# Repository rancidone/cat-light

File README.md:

# CatLight

A cat-shaped circuit board with RGB eyes and white LED whiskers. It started as an ESP32 night light, then became **CatLightPocket**, a small battery-powered light I can pin on and wear.

[Photos, video, and the build story](https://mattmadeitwork.com/projects/catlight/)

## CatLightPocket

Pocket uses a CH32V003 with C firmware built on ch32v003fun. It has 24 lighting patterns, including heartbeat, candle, rainbow, and lightning. Tap the button to change patterns; hold it to step through five brightness levels.

- [Firmware, build, and flashing instructions](pocket/README.md)
- [Board designs](pcb/CatLightPocket/)

## Original CatLight

The original is an ESP32 night light, about five inches tall. It serves a browser interface for brightness, lighting modes, and editing Lua patterns. Scripts can run in RAM while experimenting, then be saved to the light.

The ESP32 firmware is retired and has known bugs. Its code and design notes are here for anyone interested in the original build.

- [ESP32 firmware and setup](esp32/README.md)
- Board designs: `pcb/ESPLight-v1.*`

## Build your own

```sh
git clone https://github.com/rancidone/cat-light.git
cd cat-light
```

Follow the guide for your version above. The [hardware guide](docs/building.md) covers assembly, programming connections, and details still needing confirmation before reproducing the boards.

## License

See [LICENSE](LICENSE). ch32v003fun has its own license.

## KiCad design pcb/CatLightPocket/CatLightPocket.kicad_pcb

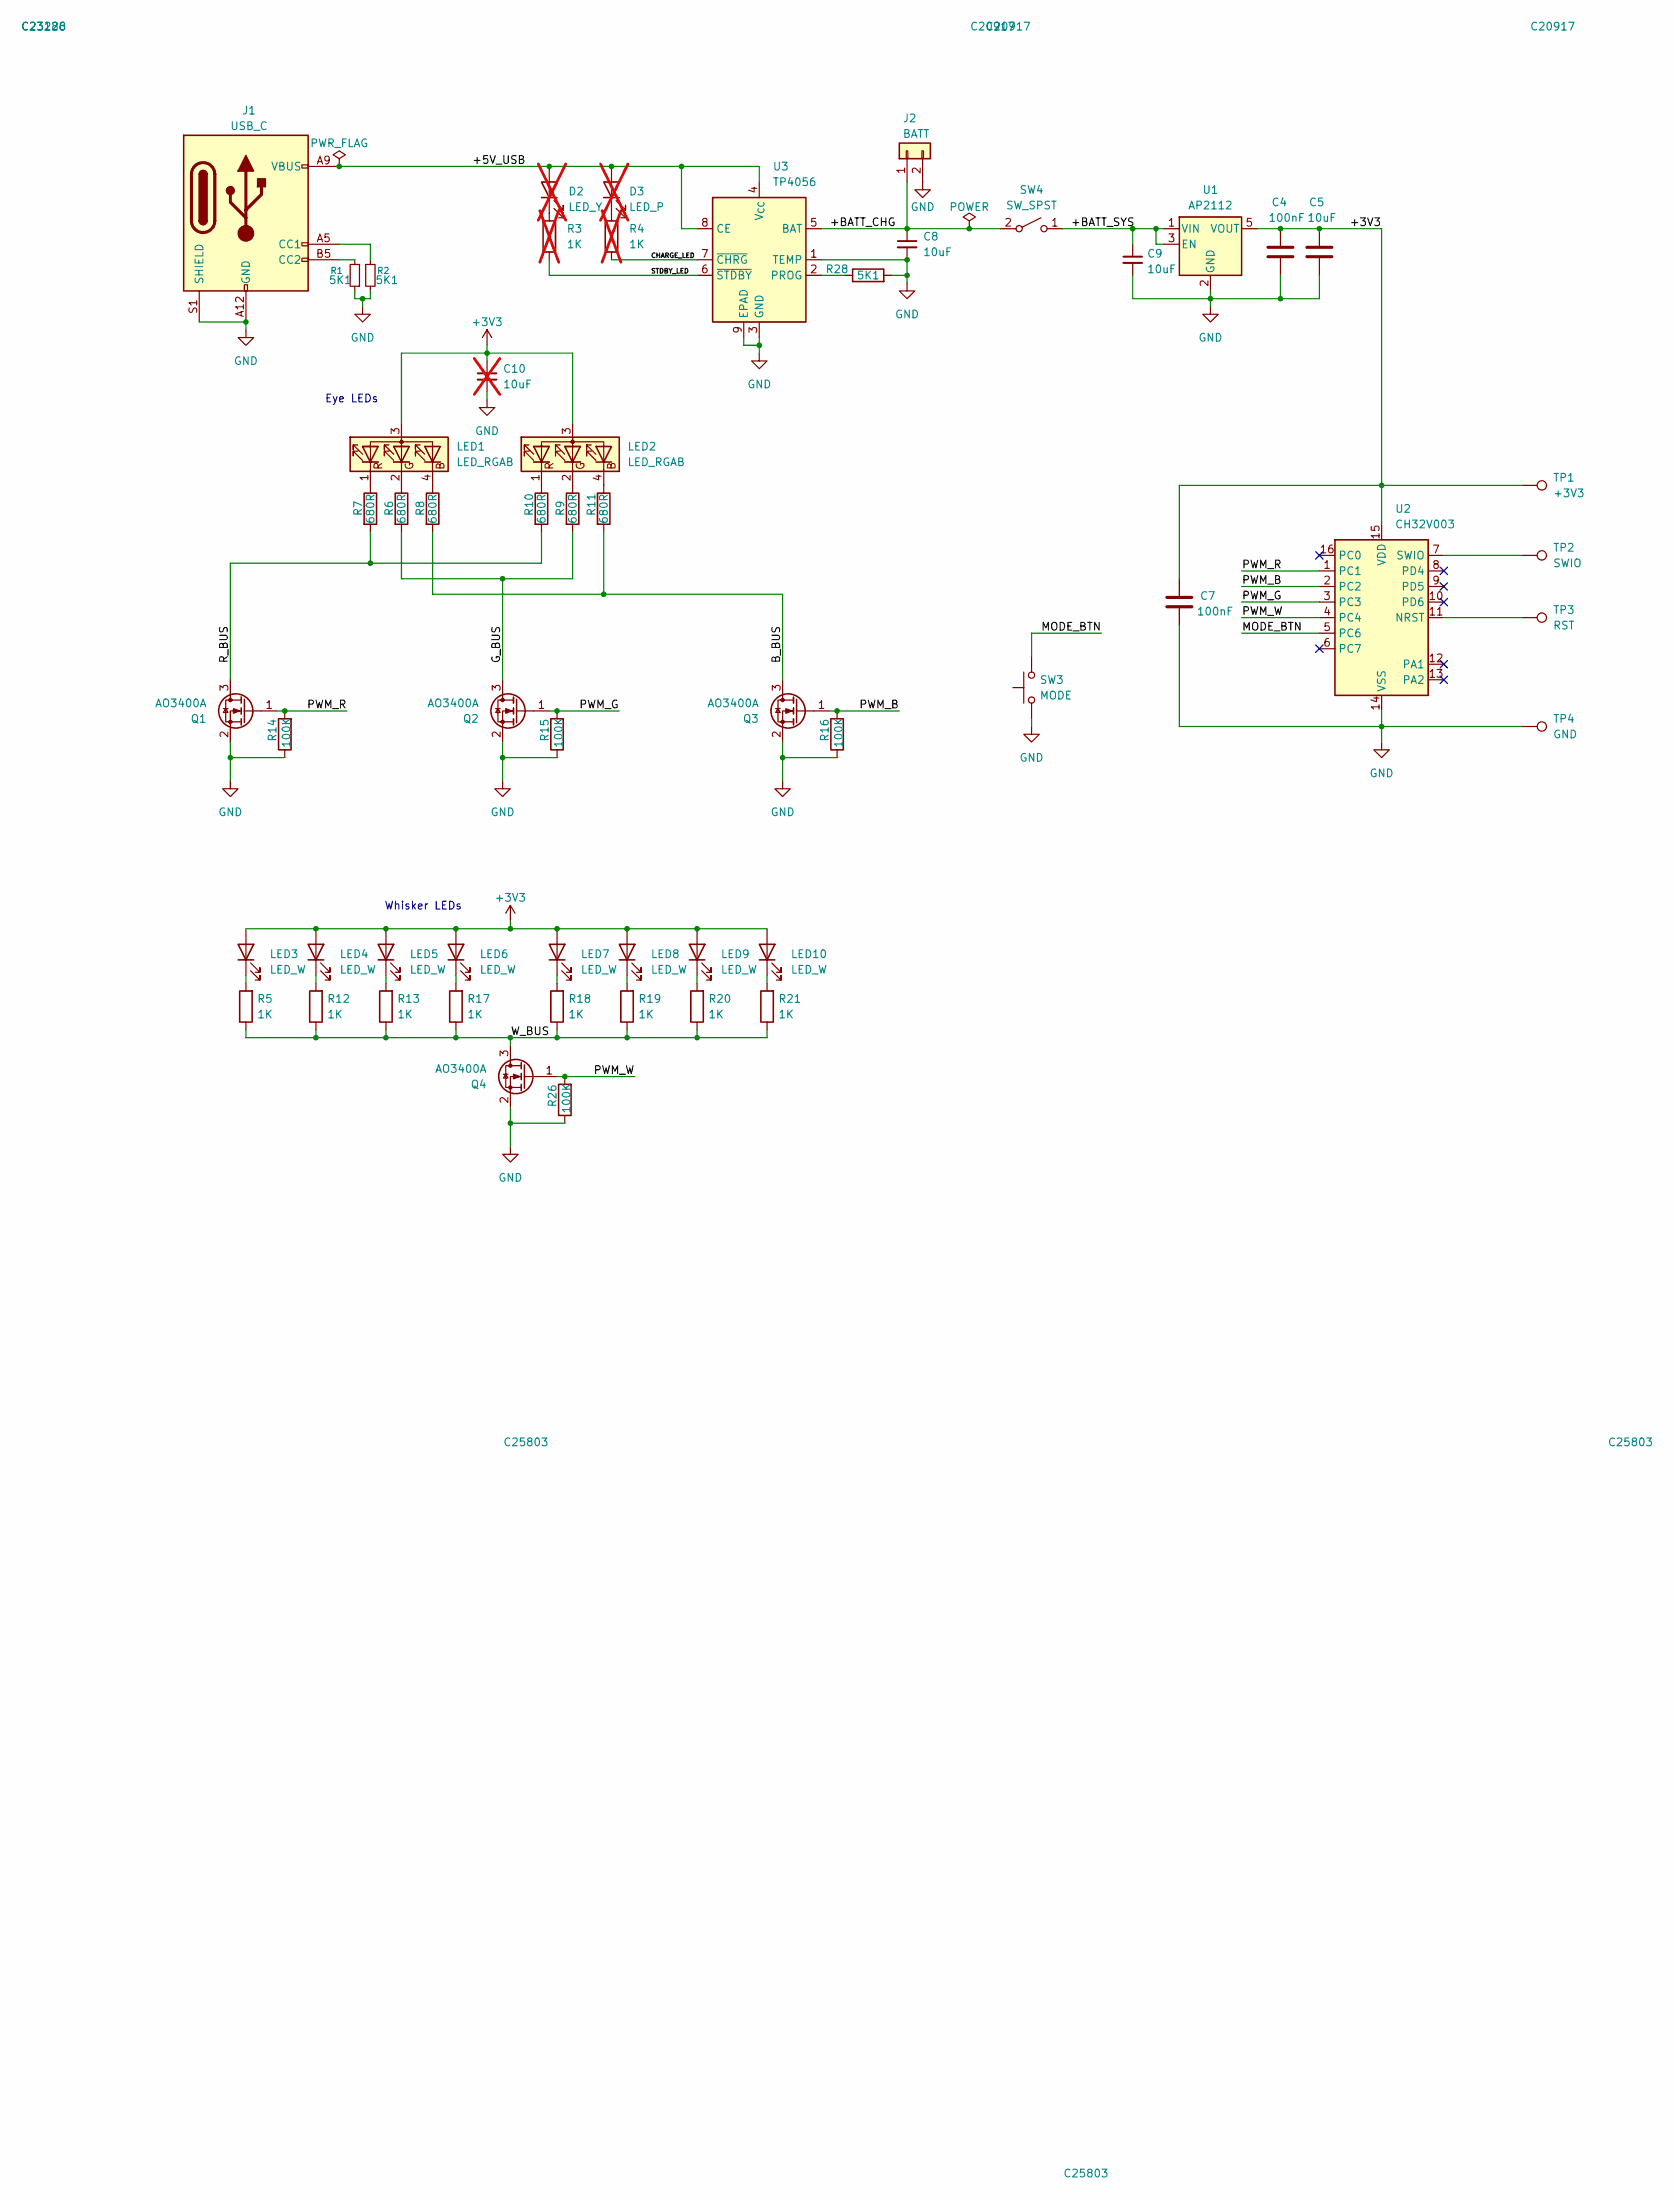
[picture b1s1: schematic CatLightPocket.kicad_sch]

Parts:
C4, C7: 100nF; C_0603_1608Metric_Pad1.08x0.95mm_HandSolder; LCSC C14663
C5: 10uF; C_0805_2012Metric_Pad1.18x1.45mm_HandSolder; LCSC C15850
C8, C9: 10uF; C_0805_2012Metric_Pad1.18x1.45mm_HandSolder
C10: 10uF; C_0805_2012Metric_Pad1.18x1.45mm_HandSolder; not fitted
D2: LED_Y; LED_0603_1608Metric_Pad1.05x0.95mm_HandSolder; not fitted
D3: LED_P; LED_0603_1608Metric_Pad1.05x0.95mm_HandSolder; not fitted
J1: USB_C; USB_C_Receptacle_HRO_TYPE-C-31-M-17
J2: BATT; JST_PH_B2B-PH-K_1x02_P2.00mm_Vertical
LED1, LED2: LED_RGAB; 0805 ARGB LED
LED3, LED4, LED5, LED6, LED7, LED8, LED9, LED10: LED_W; LED_0603_1608Metric_Pad1.05x0.95mm_HandSolder
Q1, Q2, Q3, Q4: AO3400A; SOT-23; LCSC C20917
R1, R2, R28: 5K1; R_0603_1608Metric_Pad0.98x0.95mm_HandSolder; LCSC C23186
R3, R4: 1K; R_0603_1608Metric_Pad0.98x0.95mm_HandSolder; LCSC C21190; not fitted
R5, R12, R13, R17, R18, R19, R20, R21: 1K; R_0603_1608Metric_Pad0.98x0.95mm_HandSolder; LCSC C21190
R6, R7, R8, R9, R10, R11: 680R; R_0603_1608Metric_Pad0.98x0.95mm_HandSolder; LCSC C23228
R14, R15, R16, R26: 100K; R_0603_1608Metric_Pad0.98x0.95mm_HandSolder; LCSC C25803
SW3: MODE; 6x3.5 Tactile Switch
SW4: SW_SPST; SW-MSK12C02
TP1: +3V3; TestPoint_Pad_D2.0mm
TP2: SWIO; TestPoint_Pad_D2.0mm
TP3: RST; TestPoint_Pad_D2.0mm
TP4: GND; TestPoint_Pad_D2.0mm
U1: AP2112; SOT-23-5_HandSoldering
U2: CH32V003; SOIC-16_3.9x9.9mm_P1.27mm
U3: TP4056; SOIC-8-1EP_3.9x4.9mm_P1.27mm_EP2.41x3.3mm; LCSC C16581

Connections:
+3V3: C4.1, C5.1, C7.1, C10.1, LED1.3 (A), LED2.3 (A), LED3.2 (A), LED4.2 (A), LED5.2 (A), LED6.2 (A), LED7.2 (A), LED8.2 (A), LED9.2 (A), LED10.2 (A), TP1.1 (1_1), U1.5 (VOUT), U2.15 (VDD)
/+5V_USB: D2.2 (A), D3.2 (A), J1.A9 (VBUS), J1.B9 (VBUS), U3.4 (V_{CC}), U3.8 (CE)
/+BATT_CHG: C8.1, J2.1, SW4.2 (A), U3.5 (BAT)
/+BATT_SYS: C9.1, SW4.1 (B), U1.1 (VIN), U1.3 (EN)
/B_BUS: Q3.3 (D), R8.2, R11.2
/CHARGE_LED: R4.1, U3.7 (~CHRG)
/G_BUS: Q2.3 (D), R6.2, R9.2
/MODE_BTN: SW3.2, U2.5 (PC6)
/PWM_B: Q3.1 (G), R16.2, U2.2 (PC2)
/PWM_G: Q2.1 (G), R15.2, U2.3 (PC3)
/PWM_R: Q1.1 (G), R14.2, U2.1 (PC1)
/PWM_W: Q4.1 (G), R26.2, U2.4 (PC4)
/R_BUS: Q1.3 (D), R7.2, R10.2
/STDBY_LED: R3.1, U3.6 (~STDBY)
/W_BUS: Q4.3 (D), R5.1, R12.1, R13.1, R17.1, R18.1, R19.1, R20.1, R21.1
GND: C4.2, C5.2, C7.2, C8.2, C9.2, C10.2, J1.A12 (GND), J1.B12 (GND), J1.S1 (SHIELD), J2.2, Q1.2 (S), Q2.2 (S), Q3.2 (S), Q4.2 (S), R1.1, R2.2, R14.1, R15.1, R16.1, R26.1, R28.2, SW3.1, TP4.1 (1_1), U1.2 (GND), U2.14 (VSS), U3.1 (TEMP), U3.3 (GND), U3.9 (EPAD)
unnamed: D2.1 (K), R3.2
unnamed: D3.1 (K), R4.2
unnamed: J1.A5 (CC1), R2.1
unnamed: J1.B5 (CC2), R1.2
unnamed: LED1.4 (BK), R8.1
unnamed: LED1.2 (GK), R6.1
unnamed: LED1.1 (RK), R7.1
unnamed: LED2.4 (BK), R11.1
unnamed: LED2.2 (GK), R9.1
unnamed: LED2.1 (RK), R10.1
unnamed: LED3.1 (K), R5.2
unnamed: LED4.1 (K), R12.2
unnamed: LED5.1 (K), R13.2
unnamed: LED6.1 (K), R17.2
unnamed: LED7.1 (K), R18.2
unnamed: LED8.1 (K), R19.2
unnamed: LED9.1 (K), R20.2
unnamed: LED10.1 (K), R21.2
unnamed: TP2.1 (1_1), U2.7 (SWIO)
unnamed: TP3.1 (1_1), U2.11 (NRST)
unnamed: R28.1, U3.2 (PROG)

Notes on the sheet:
Eye LEDs
Whisker LEDs

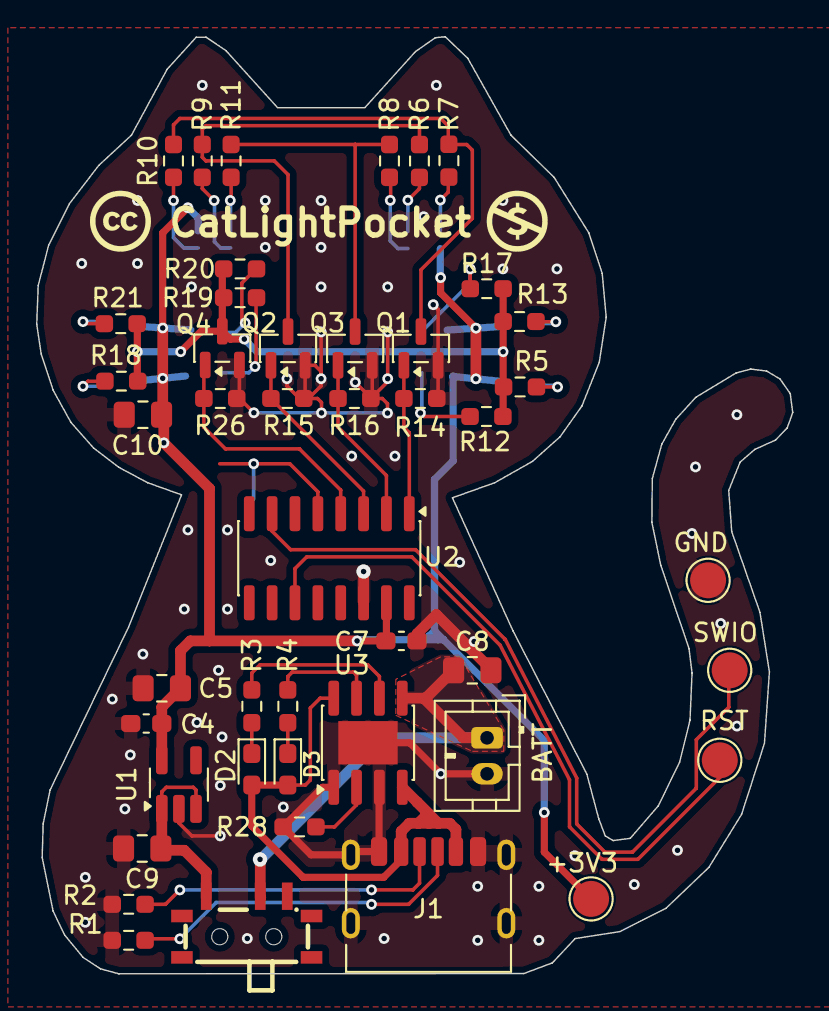
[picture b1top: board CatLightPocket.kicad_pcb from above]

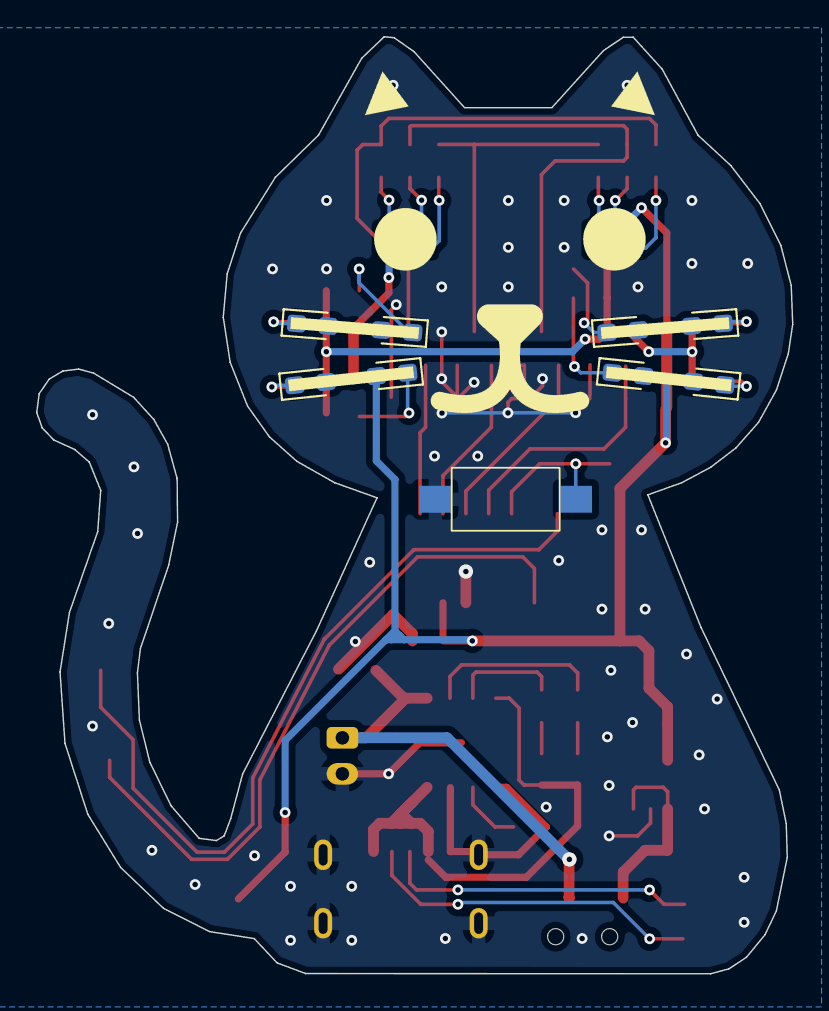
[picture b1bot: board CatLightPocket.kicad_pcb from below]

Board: 2 copper layers, 42.0 x 52.1 mm, 56 parts (11 on the bottom side), 37 nets.

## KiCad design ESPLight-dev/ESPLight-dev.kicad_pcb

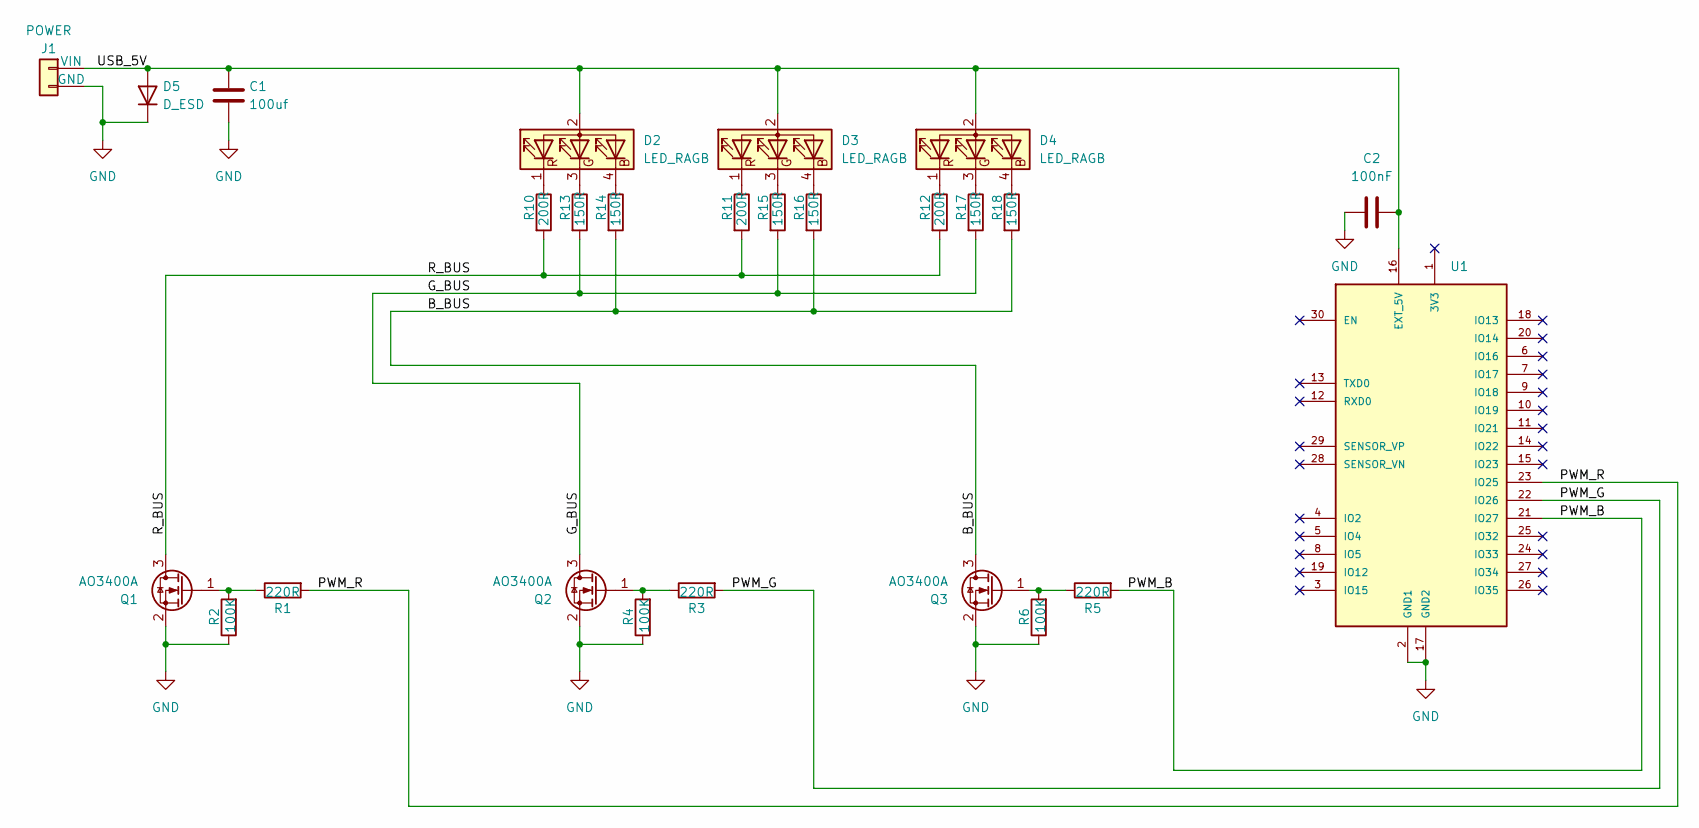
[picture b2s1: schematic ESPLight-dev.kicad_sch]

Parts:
C1: 100uf; C_Radial_D6.3mm_H5.0mm_P2.50mm
C2: 100nF; C_0603_1608Metric
D2, D3, D4: LED_RAGB; LED_D5.0mm-4_RGB
D5: D_ESD; D_SOD-523
J1: POWER; PinHeader_1x02_P2.54mm_Vertical
Q1, Q2, Q3: AO3400A; SOT-23
R1, R3, R5: 220R; R_0603_1608Metric
R2, R4, R6: 100K; R_0603_1608Metric
R10, R11, R12: 200R; R_0603_1608Metric
R13, R14, R15, R16, R17, R18: 150R; R_0603_1608Metric
U1: DEVKIT_V1_ESP32-WROOM-32; ESP32_30pin

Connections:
/B_BUS: Q3.3 (D), R14.2, R16.2, R18.2
/G_BUS: Q2.3 (D), R13.2, R15.2, R17.2
/PWM_B: R5.2, U1.21 (IO27)
/PWM_G: R3.2, U1.22 (IO26)
/PWM_R: R1.2, U1.23 (IO25)
/R_BUS: Q1.3 (D), R10.2, R11.2, R12.2
/USB_5V: C1.1, C2.2, D2.2 (A), D3.2 (A), D4.2 (A), D5.2 (A), J1.1 (VIN), U1.16 (EXT_5V)
GND: C1.2, C2.1, D5.1 (K), J1.2 (GND), Q1.2 (S), Q2.2 (S), Q3.2 (S), R2.1, R4.1, R6.1, U1.2 (GND1), U1.17 (GND2)
unnamed: D2.4 (BK), R14.1
unnamed: D2.3 (GK), R13.1
unnamed: D2.1 (RK), R10.1
unnamed: D3.4 (BK), R16.1
unnamed: D3.3 (GK), R15.1
unnamed: D3.1 (RK), R11.1
unnamed: D4.4 (BK), R18.1
unnamed: D4.3 (GK), R17.1
unnamed: D4.1 (RK), R12.1
unnamed: Q1.1 (G), R1.1, R2.2
unnamed: Q2.1 (G), R3.1, R4.2
unnamed: Q3.1 (G), R5.1, R6.2

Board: 2 copper layers, 26 parts (0 on the bottom side), 20 nets, no tracks yet.

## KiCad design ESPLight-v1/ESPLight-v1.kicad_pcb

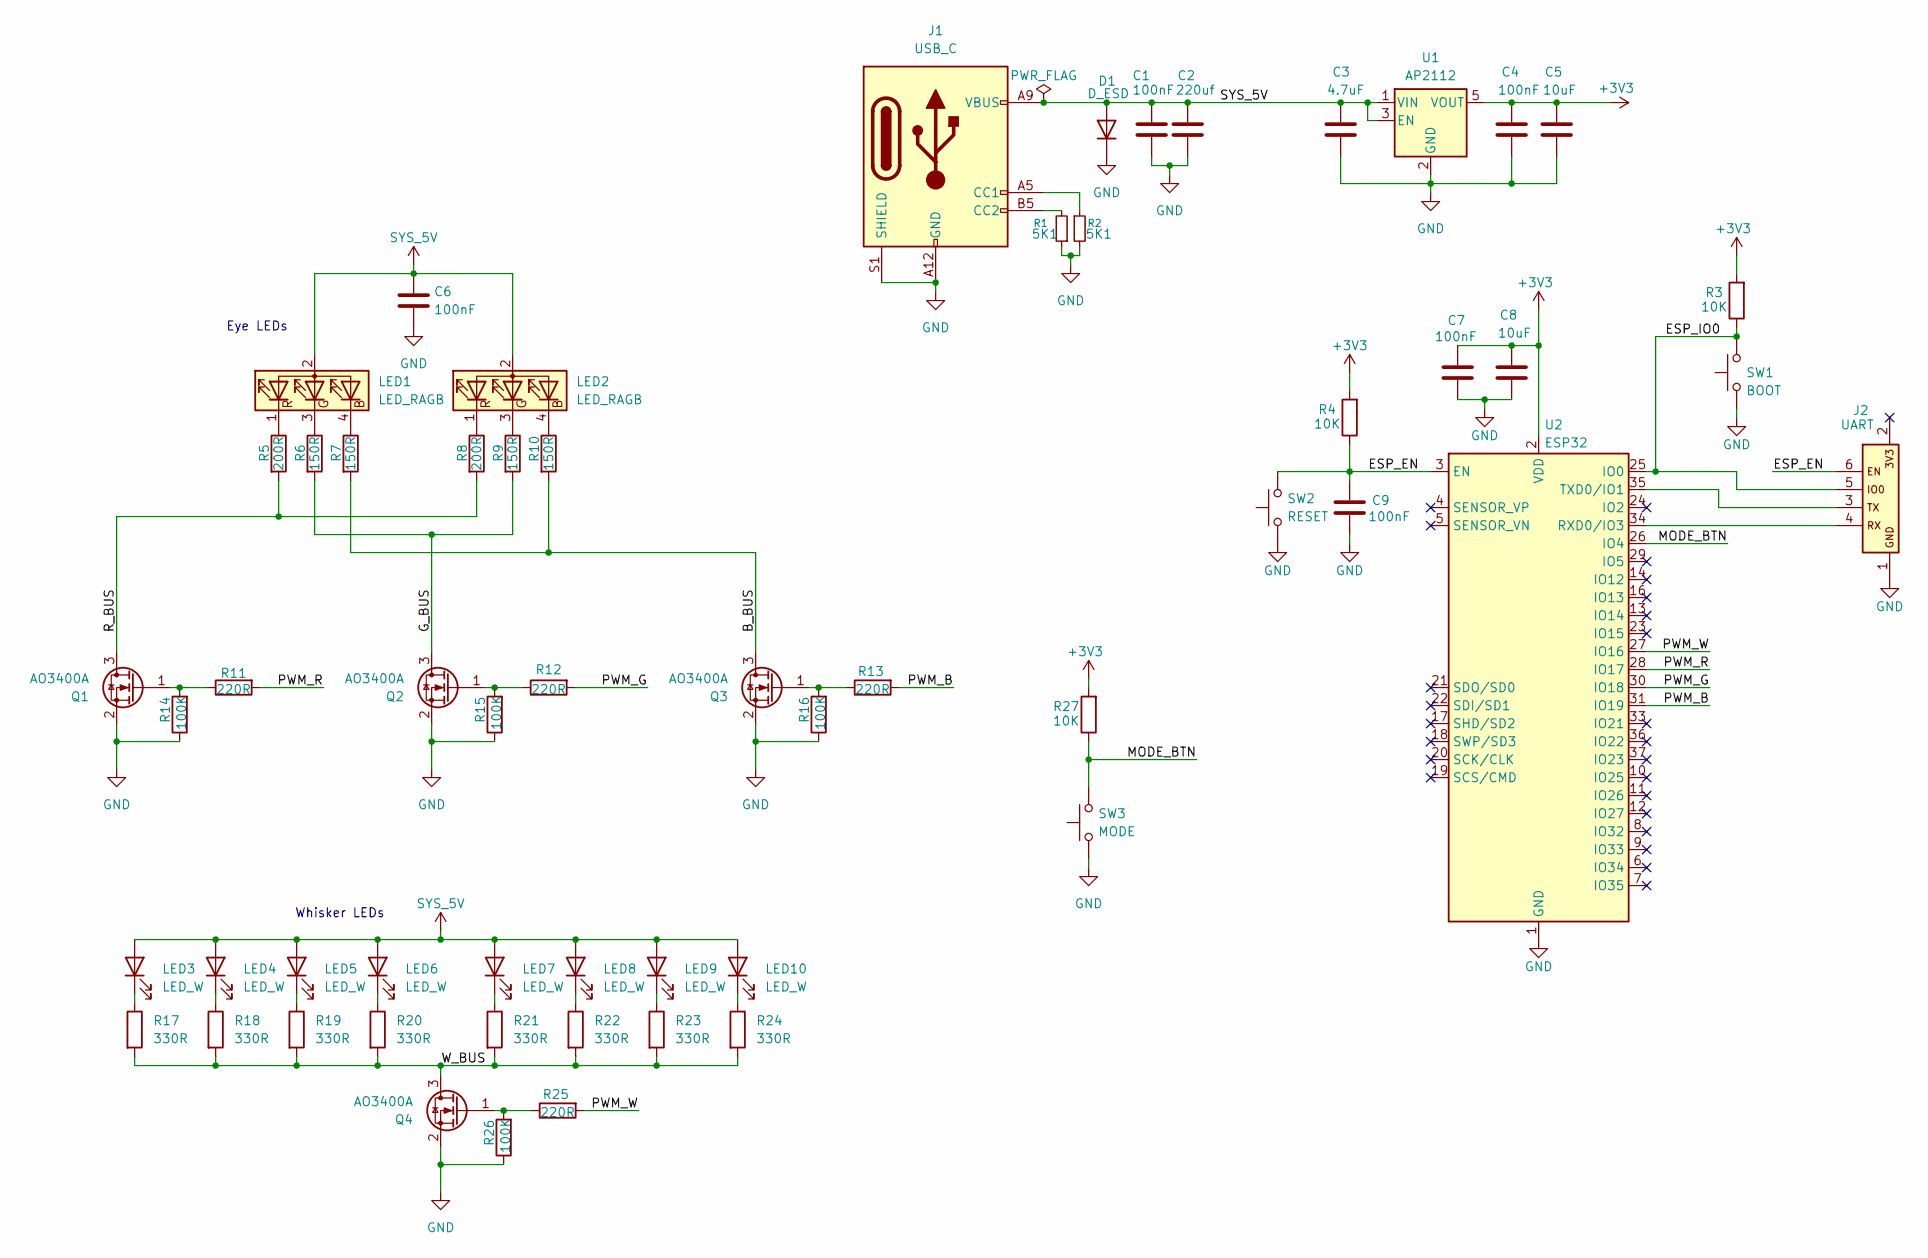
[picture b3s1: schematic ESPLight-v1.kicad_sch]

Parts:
C1, C4, C6, C7, C9: 100nF; C_0603_1608Metric_Pad1.08x0.95mm_HandSolder
C2: 220uf; C_Radial_D6.3mm_H5.0mm_P2.50mm
C3: 4.7uF; C_0805_2012Metric_Pad1.18x1.45mm_HandSolder
C5, C8: 10uF; C_0805_2012Metric_Pad1.18x1.45mm_HandSolder
D1: D_ESD; D_SOD-523
J1: USB_C; USB_C_Receptacle_HRO_TYPE-C-31-M-17
J2: UART; PinHeader_2x03_P2.54mm_Horizontal
LED1, LED2: LED_RAGB; LED_D5.0mm-4_RGB
LED3, LED4, LED5, LED6, LED7, LED8, LED9, LED10: LED_W; LED_0603_1608Metric_Pad1.05x0.95mm_HandSolder
Q1, Q2, Q3, Q4: AO3400A; SOT-23
R1, R2: 5K1; R_0603_1608Metric_Pad0.98x0.95mm_HandSolder
R3, R4, R27: 10K; R_0603_1608Metric_Pad0.98x0.95mm_HandSolder
R5, R8: 200R; R_0603_1608Metric_Pad0.98x0.95mm_HandSolder
R6, R7, R9, R10: 150R; R_0603_1608Metric_Pad0.98x0.95mm_HandSolder
R11, R12, R13, R25: 220R; R_0603_1608Metric_Pad0.98x0.95mm_HandSolder
R14, R15, R16, R26: 100K; R_0603_1608Metric_Pad0.98x0.95mm_HandSolder
R17, R18, R19, R20, R21, R22, R23, R24: 330R; R_0603_1608Metric_Pad0.98x0.95mm_HandSolder
SW1: BOOT; SW_Tactile_SPST_6x3.5mm
SW2: RESET; SW_Tactile_SPST_6x3.5mm
SW3: MODE; SW_Tactile_SPST_6x3.5mm
U1: AP2112; SOT-23-5_HandSoldering
U2: ESP32; ESP32-WROOM-32_NoThermal

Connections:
+3V3: C4.1, C5.1, C7.1, C8.1, R3.2, R4.2, R27.2, U1.5 (VOUT), U2.2 (VDD)
/B_BUS: Q3.3 (D), R7.2, R10.2
/ESP_EN: C9.1, J2.6 (EN), R4.1, SW2.2, U2.3 (EN)
/ESP_IO0: J2.5 (IO0), R3.1, SW1.2, U2.25 (IO0)
/G_BUS: Q2.3 (D), R6.2, R9.2
/MODE_BTN: R27.1, SW3.2, U2.26 (IO4)
/PWM_B: R13.2, U2.31 (IO19)
/PWM_G: R12.2, U2.30 (IO18)
/PWM_R: R11.2, U2.28 (IO17)
/PWM_W: R25.2, U2.27 (IO16)
/R_BUS: Q1.3 (D), R5.2, R8.2
/W_BUS: Q4.3 (D), R17.2, R18.2, R19.2, R20.2, R21.2, R22.2, R23.2, R24.2
GND: C1.2, C2.2, C3.2, C4.2, C5.2, C6.2, C7.2, C8.2, C9.2, D1.1 (K), J1.A12 (GND), J1.B12 (GND), J1.S1 (SHIELD), J2.1 (GND), Q1.2 (S), Q2.2 (S), Q3.2 (S), Q4.2 (S), R1.1, R2.2, R14.1, R15.1, R16.1, R26.1, SW1.1, SW2.1, SW3.1, U1.2 (GND), U2.1 (GND), U2.15 (GND), U2.38 (GND), U2.39 (GND)
unnamed: J1.A5 (CC1), R2.1
unnamed: J1.B5 (CC2), R1.2
unnamed: J2.4 (RX), U2.34 (RXD0/IO3)
unnamed: J2.3 (TX), U2.35 (TXD0/IO1)
unnamed: LED1.4 (BK), R7.1
unnamed: LED1.3 (GK), R6.1
unnamed: LED1.1 (RK), R5.1
unnamed: LED2.4 (BK), R10.1
unnamed: LED2.3 (GK), R9.1
unnamed: LED2.1 (RK), R8.1
unnamed: LED3.1 (K), R17.1
unnamed: LED4.1 (K), R18.1
unnamed: LED5.1 (K), R19.1
unnamed: LED6.1 (K), R20.1
unnamed: LED7.1 (K), R21.1
unnamed: LED8.1 (K), R22.1
unnamed: LED9.1 (K), R23.1
unnamed: LED10.1 (K), R24.1
unnamed: Q1.1 (G), R11.1, R14.2
unnamed: Q2.1 (G), R12.1, R15.2
unnamed: Q3.1 (G), R13.1, R16.2
unnamed: Q4.1 (G), R25.1, R26.2
SYS_5V: C1.1, C2.1, C3.1, C6.1, D1.2 (A), J1.A9 (VBUS), J1.B9 (VBUS), LED1.2 (A), LED2.2 (A), LED3.2 (A), LED4.2 (A), LED5.2 (A), LED6.2 (A), LED7.2 (A), LED8.2 (A), LED9.2 (A), LED10.2 (A), U1.1 (VIN), U1.3 (EN)

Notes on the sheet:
Eye LEDs
Whisker LEDs

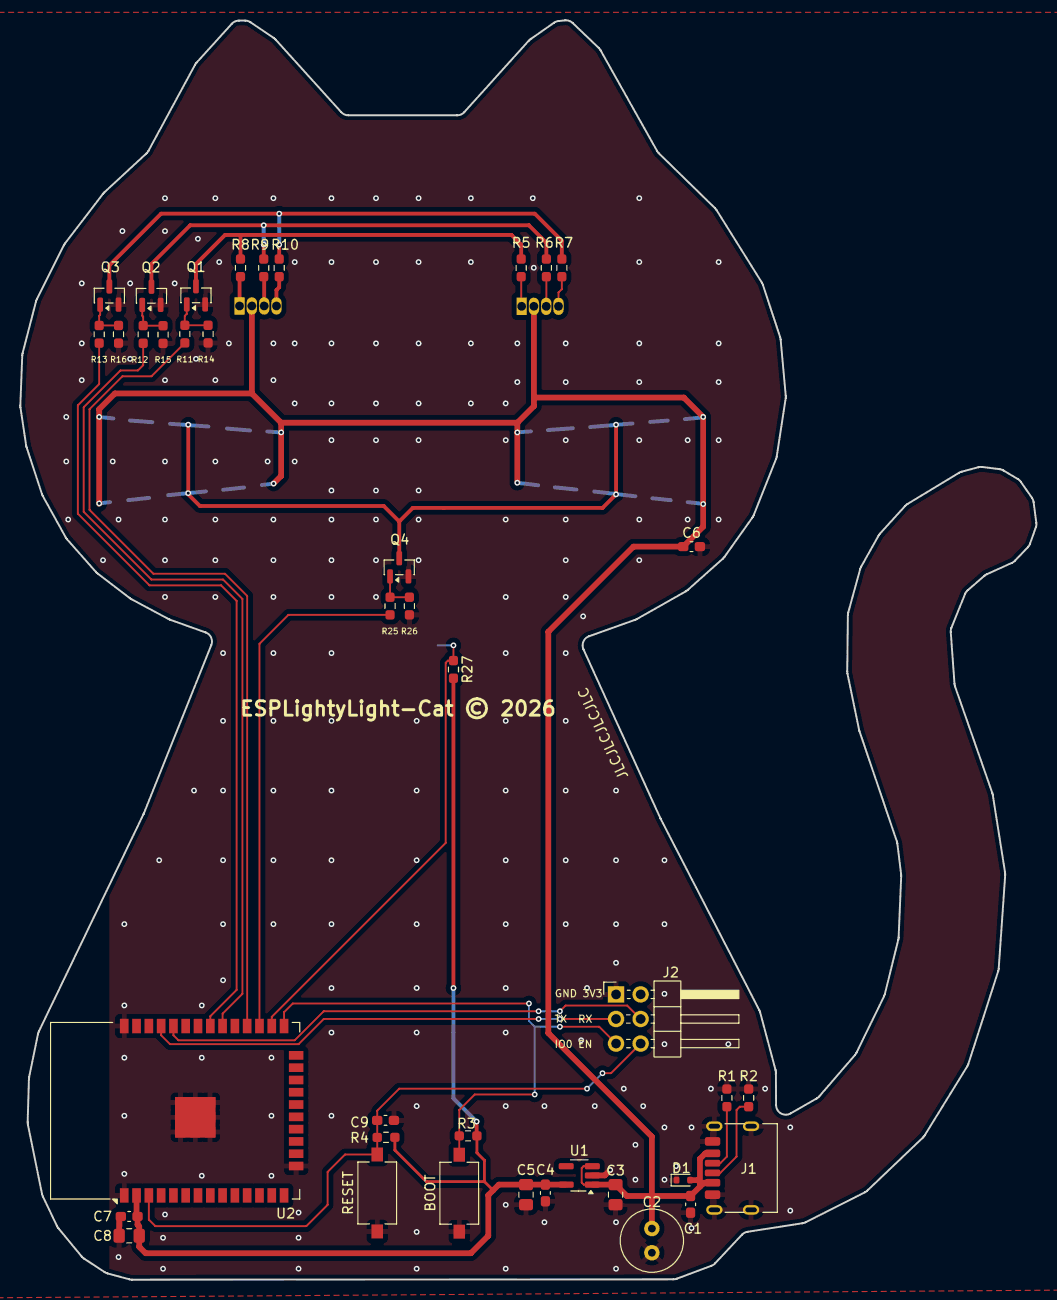
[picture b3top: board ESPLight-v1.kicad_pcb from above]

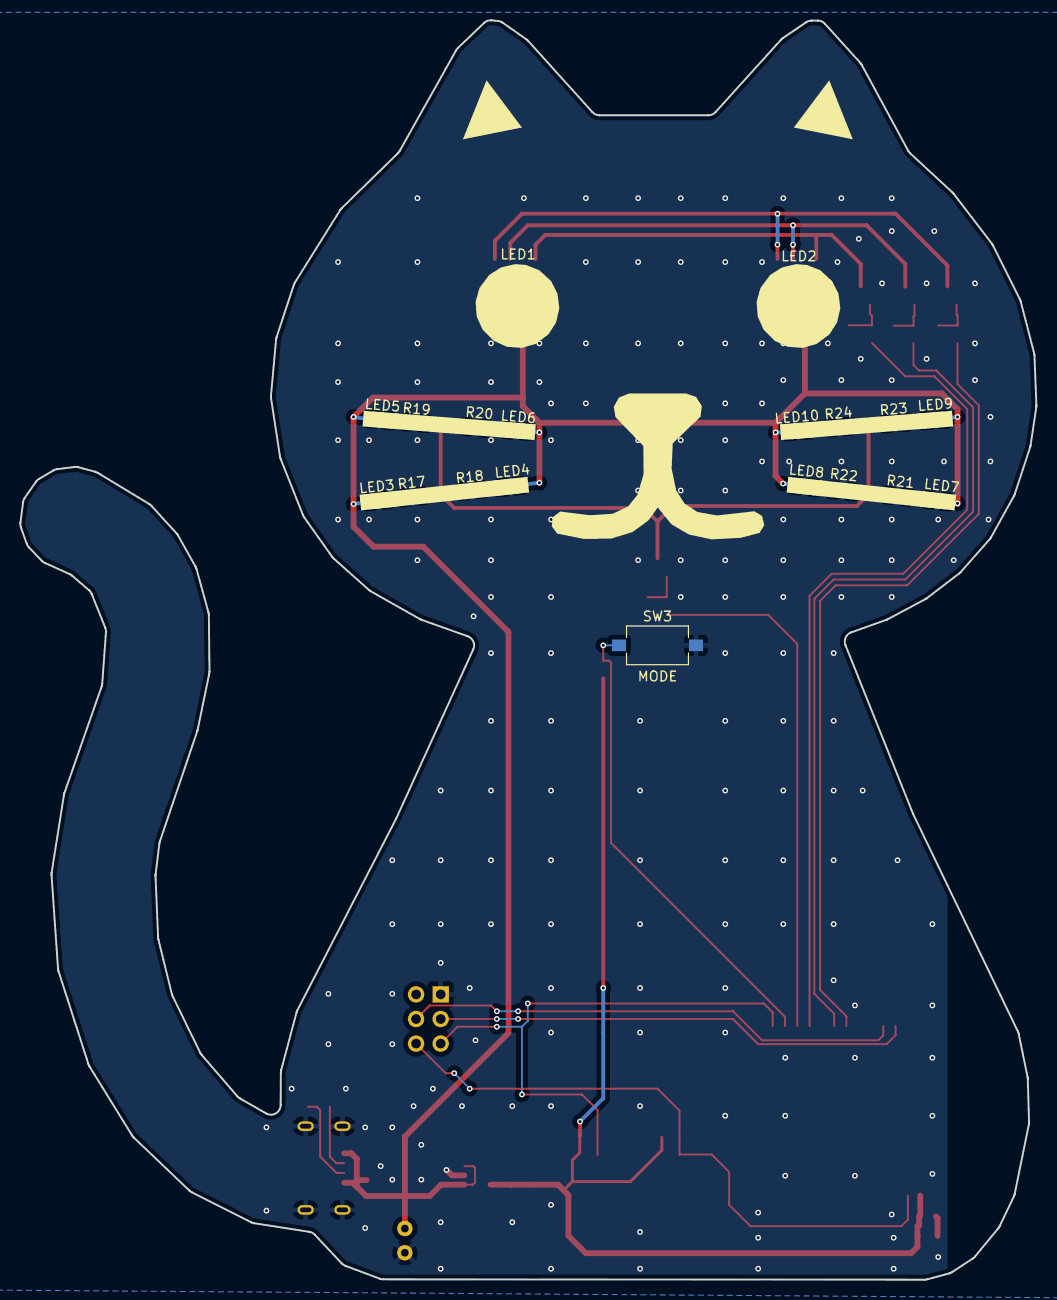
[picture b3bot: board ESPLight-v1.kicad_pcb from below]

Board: 2 copper layers, 105.0 x 130.1 mm, 58 parts (19 on the bottom side), 36 nets.

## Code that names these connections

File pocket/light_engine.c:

#include "light_engine.h"
#include "ch32v003fun/ch32fun/ch32fun.h"

/*
 * Pin assignments (confirmed from schematic):
 *   PC1 → PWM_R  (TIM2 CH4, partial remap 1)
 *   PC2 → PWM_B  (TIM2 CH2, partial remap 1)
 *   PC3 → PWM_G  (TIM1 CH3, no remap)
 *   PC4 → PWM_W  (TIM1 CH4, no remap)
 *   PC6 → MODE_BTN (input, active low, external pull-up)
 *
 * PWM: 48 MHz / (PSC+1) / (ARR+1) = 48e6 / 1 / 4800 = 10 kHz
 */

#define PWM_ARR 4799u

static float s_brightness = 0.30f; /* medium — index 2 of 5 */

static inline uint32_t duty(uint8_t val)  { return (uint32_t)(val  * s_brightness * PWM_ARR / 255u); }
static inline uint32_t dutyf(float v)     { return (uint32_t)(v    * s_brightness * 0.5f * PWM_ARR); }

void light_engine_set_brightness(float b) { s_brightness = b; }

void light_engine_init(void)
{
    /* Clocks */
    RCC->APB2PCENR |= RCC_APB2Periph_GPIOC | RCC_APB2Periph_AFIO | RCC_APB2Periph_TIM1;
    RCC->APB1PCENR |= RCC_APB1Periph_TIM2;

    /* TIM2 partial remap 1: CH2→PC2, CH4→PC1 */
    AFIO->PCFR1 = (AFIO->PCFR1 & ~AFIO_PCFR1_TIM2_REMAP) | AFIO_PCFR1_TIM2_REMAP_PARTIALREMAP1;

    /* GPIO: PC1/PC2/PC3/PC4 → AF push-pull 50 MHz (CNF=10, MODE=11 → 0xB) */
    uint32_t cfg = GPIOC->CFGLR;
    cfg &= ~(0xFFFFu << 4);   /* clear PC1..PC4 nibbles */
    cfg |= (0xBBBBu << 4);    /* set all four to AF push-pull */
    /* PC6 → input with pull-up (CNF=10, MODE=00 → 0x8), OUTDR bit set for pull-up */
    cfg &= ~(0xFu << 24);
    cfg |= (0x8u << 24);
    GPIOC->CFGLR = cfg;
    GPIOC->OUTDR |= (1u << 6); /* enable internal pull-up on PC6 */

    /* TIM2: CH2 (PWM_B / PC2) and CH4 (PWM_R / PC1) */
    TIM2->PSC    = 0;
    TIM2->ATRLR  = PWM_ARR;
    /* CH2 PWM mode 1, preload enable — OC2M at [14:12], OC2PE at [11] */
    TIM2->CHCTLR1 = (0x6u << 12) | (1u << 11);
    /* CH4 PWM mode 1, preload enable — OC4M at [14:12], OC4PE at [11] */
    TIM2->CHCTLR2 = (0x6u << 12) | (1u << 11);
    TIM2->CCER   = TIM_CC2E | TIM_CC4E;
    TIM2->CH2CVR = 0;
    TIM2->CH4CVR = 0;
    TIM2->CTLR1  = TIM_ARPE | TIM_CEN;

    /* TIM1: CH3 (PWM_G / PC3) and CH4 (PWM_W / PC4), no remap */
    TIM1->PSC    = 0;
    TIM1->ATRLR  = PWM_ARR;
    /* CH3 PWM mode 1, preload enable */
    /* CH3: OC3M at [6:4], OC3PE at [3] — CH4: OC4M at [14:12], OC4PE at [11] */
    TIM1->CHCTLR2 = (0x6u << 4) | (1u << 3)
                  | (0x6u << 12) | (1u << 11);
    TIM1->CCER   = TIM_CC3E | TIM_CC4E;
    TIM1->CH3CVR = 0;
    TIM1->CH4CVR = 0;
    TIM1->BDTR   = TIM_MOE;
    TIM1->CTLR1  = TIM_ARPE | TIM_CEN;
}

void light_engine_write(const light_frame_t *frame)
{
    TIM2->CH4CVR = duty(frame->eye_r);   /* PC1 */
    TIM2->CH2CVR = duty(frame->eye_b);   /* PC2 */
    TIM1->CH3CVR = duty(frame->eye_g);   /* PC3 */
    TIM1->CH4CVR = dutyf(frame->whisker < 0.0f ? 0.0f :
                          frame->whisker > 1.0f ? 1.0f : frame->whisker); /* PC4 */
}

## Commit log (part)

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2026-03-18 Move pcb files
2026-03-19 MVP firmware
2026-03-20 firmware update, demo modes
2026-03-25 Add v2 design docs, project config, and Claude tooling
2026-03-25 Gitignore docs/summaries/ and untrack handoff files
2026-03-25 Add testing brief, fix handoff filename format, update references
2026-03-25 Refactor firmware: v2 architecture with scripting, wifi, persistence
    - Remove behavior.c/h/behavior_types.h; replace with mode_manager rewrite
    - Add boot, persistence, scripting_engine, wifi_web modules
    - Add partitions.csv for NVS support
    - Update CMakeLists, idf_component.yml, dependencies.lock
    - Update CLAUDE.md, TODO.md, and tooling
2026-04-03 Move project info to AGENTS.md
2026-04-03 Remove tracked .envrc
2026-04-03 Complete mode control API and mark designs implemented
2026-05-25 Add captive portal, web UI, cjson, and CatLightPocket PCB
    - Add DNS server task for SoftAP captive portal (redirects all queries to 192.168.4.1)
    - Add HTTP redirects for common captive-portal probe URIs
    - Fix wifi credential handler: copy strings before freeing cJSON tree, reboot on save
    - Switch from idf json component to espressif/cjson; add to dependencies
    - Add littlefs partition image build step and sdkconfig.defaults for 4MB flash
    - Fix minimum brightness floor (0.0f → 0.001f to prevent fully-off on dim)
2026-05-25 Add CH32V003 pocket firmware (ch32v003fun, bare-metal)
    Ports the three built-in light modes (fade, spooky, rainbow) to the
    CatLightPocket board. No RTOS, no networking, no scripting engine —
    just a 33 Hz main loop with SysTick timing and TIM1/TIM2 PWM output.
    Pin assignments (from schematic):
    PC1 → PWM_R TIM2_CH4, partial remap 1
    PC2 → PWM_B TIM2_CH2, partial remap 1
2026-05-25 Fix pocket build: rename main.c, add funconfig.h, fix timing and math linking
2026-05-25 Reorganize: move ESP32 firmware into esp32/, update CLAUDE.md
2026-05-25 Add wch-link-rv-mode.py to switch LinkE to RISC-V mode on macOS
2026-05-25 Fix PWM CHCTLR bit shifts, add board-test firmware
2026-05-25 24 modes, replace fade with heartbeat, tune brightness
2026-05-25 Add hold-button brightness control — 5 levels, medium default

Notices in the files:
ESPLight-v1/ESPLight-v1.kicad_pcb:
ESPLightyLight-Cat © 2026
